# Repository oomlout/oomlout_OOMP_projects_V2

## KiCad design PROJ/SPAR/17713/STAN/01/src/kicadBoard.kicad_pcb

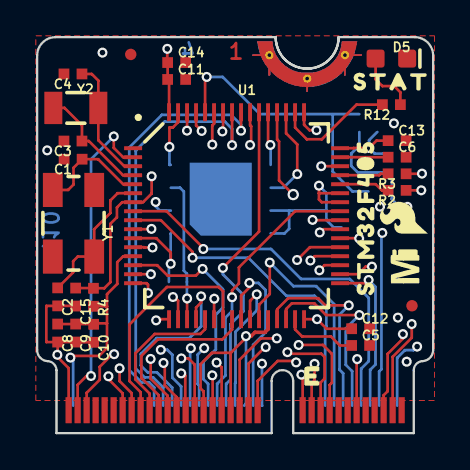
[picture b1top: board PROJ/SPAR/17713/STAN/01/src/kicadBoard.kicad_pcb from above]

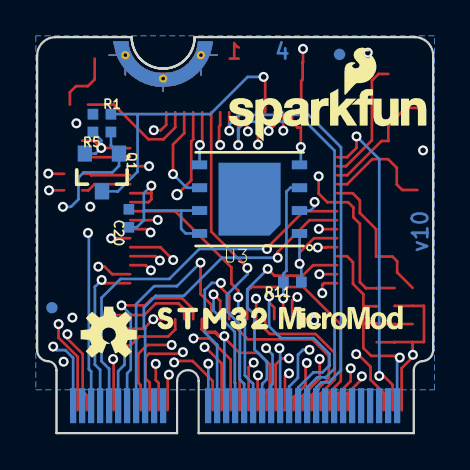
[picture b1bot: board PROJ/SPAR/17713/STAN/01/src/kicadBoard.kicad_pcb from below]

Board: 4 copper layers, 22.0 x 22.0 mm, 43 parts (12 on the bottom side), 58 nets.

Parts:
C1, C2: 22pF; 0402-TIGHT
C3, C4: 15pF; 0402-TIGHT
C5, C6: 2.2uF; 0402-TIGHT
C8, C11, C12, C13, C14, C15, C20: 0.1uF; 0402-TIGHT
C9: 1.0uF; 0402-TIGHT
C10: 4.7uF; 0402-TIGHT
D5: BLUE; LED-0603
FD1, FD2, FD3, FD4: FIDUCIALUFIDUCIAL; FIDUCIAL-MICRO
FRAME1: FRAME-LETTER; CREATIVE_COMMONS
J1: MICROMOD-2222; M.2-CARD-E-22
LOGO2: OSHW-LOGOS; OSHW-LOGO-S
LOGO3: SFE_LOGO_NAME_FLAME.1_INCH; SFE_LOGO_NAME_FLAME_.1
Q1: SOT23-3
R1, R5, R11: 100k; 0402-TIGHT
R2, R3: 22; 0402-TIGHT
R4: 5.1k; 0402-TIGHT
R12: 1k; 0402-TIGHT
U1: STM32F405RGT6; TQFP64
U3: W25QXX128MBIT-6X5; WSON-8-6X5
U$1: STAT0
U$2: STM320
U$3: MICROMOD_MI_LOGO_.35
U$4: STM32F4050
U$5: MICROMOD_LOGO_.3
U$6: SFE_LOGO_FLAME_.1
U$7: PRODUCTION_INSTRUCTIONS
Y1: 12MHz; CRYSTAL-SMD-5X3.2-4PAD
Y2: 32.768kHz; CRYSTAL-SMD-3.2X1.5MM

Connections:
3.3V: C8.1, C9.1, C10.1, C11.1, C12.1, C13.1, C14.1, C20.1, J1.2, J1.74, Q1.2, R4.2, R5.2, R11.2, U1.13, U1.19, U1.32, U1.42, U1.43, U1.48, U1.64, U3.3, U3.7, U3.8
A0: J1.34, U1.25
A1: J1.38, U1.26
AUD_BCLK: J1.50, U1.55
AUD_IN: J1.54, U1.57
AUD_LRCLK: J1.52, U1.20
AUD_OUT: J1.56, U1.56
BATT_VIN: J1.49, U1.15
BOOT0: Q1.3, R1.2, U1.60
CAN_RX: J1.41, U1.61
CAN_TX: J1.43, U1.62
CIPO: J1.61, U1.22
COPI: J1.59, U1.23
D0: J1.10, U1.8
D1: J1.18, U1.9
D+: J1.3, R3.1
D-: J1.5, R2.1
FLASH_SCK: U1.51, U3.6
FLASH_SDI: U1.53, U3.5
FLASH_SDO: U1.52, U3.2
FLASH_~CS: R11.1, U1.11, U3.1
G0: J1.40, U1.54
G1: J1.42, U1.41
G2: J1.44, U1.14
G3: J1.46, U1.39
G4: J1.48, U1.40
G5: J1.73, U1.2
G6: J1.71, U1.10
GND: C1.2, C2.2, C3.2, C4.2, C5.2, C6.2, C8.2, C9.2, C10.2, C11.2, C12.2, C13.2, C14.2, C15.2, C20.2, D5.C, J1.1, J1.7, J1.33, J1.36, J1.39, J1.45, J1.75, J1.GND1, J1.GND2, J1.GND3, R1.1, U1.12, U1.18, U1.28, U1.63, U3.4
HOST_D+: J1.35, U1.36
HOST_D-: J1.37, U1.35
HOST_ID: J1.8, U1.33
HOST_VBUS: J1.63, U1.34
unnamed: D5.A, R12.1
unnamed: R2.2, U1.44
unnamed: R3.2, U1.45
unnamed: C4.1, U1.3, Y2.P$2
unnamed: C3.1, U1.4, Y2.P$1
unnamed: C2.1, U1.6, Y1.3
unnamed: C1.1, U1.5, Y1.1
unnamed: C6.1, U1.47
unnamed: C5.1, U1.31
PWM0: J1.32, U1.37
PWM1: J1.47, U1.38
RX1: J1.19, U1.17
SCK: J1.57, U1.21
SCL: J1.14, U1.29
SCL1: J1.53, U1.58
SDA: J1.12, U1.30
SDA1: J1.51, U1.59
STAT: R12.2, U1.50
SWCLK: J1.21, U1.49
SWDIO: J1.23, U1.46
TX1: J1.17, U1.16
~BOOT: J1.11, Q1.1, R5.1
~CS: J1.55, U1.24
~INT: J1.16, U1.27
~RESET: C15.1, J1.6, R4.1, U1.7

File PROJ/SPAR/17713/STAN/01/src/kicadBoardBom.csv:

"Id";"Designator";"Package";"Quantity";"Designation";"Supplier and ref";
1;"R12";"0402-TIGHT";1;"1k";;;
2;"Y1";"CRYSTAL-SMD-5X3.2-4PAD";1;"12MHz";;;
3;"U$6";"SFE_LOGO_FLAME_.1";1;"";;;
4;"FRAME1";"CREATIVE_COMMONS";1;"FRAME-LETTER";;;
5;"R2,R3";"0402-TIGHT";2;"22";;;
6;"D5";"LED-0603";1;"BLUE";;;
7;"FD1,FD4,FD2,FD3";"FIDUCIAL-MICRO";4;"FIDUCIALUFIDUCIAL";;;
8;"C6,C5";"0402-TIGHT";2;"2.2uF";;;
9;"U$1";"STAT0";1;"";;;
10;"Y2";"CRYSTAL-SMD-3.2X1.5MM";1;"32.768kHz";;;
11;"C10";"0402-TIGHT";1;"4.7uF";;;
12;"C12,C14,C11,C8,C13,C15,C20";"0402-TIGHT";7;"0.1uF";;;
13;"J1";"M.2-CARD-E-22";1;"MICROMOD-2222";;;
14;"C2,C1";"0402-TIGHT";2;"22pF";;;
15;"C3,C4";"0402-TIGHT";2;"15pF";;;
16;"U1";"TQFP64";1;"STM32F405RGT6";;;
17;"U$7";"PRODUCTION_INSTRUCTIONS";1;"";;;
18;"U$3";"MICROMOD_MI_LOGO_.35";1;"";;;
19;"R4";"0402-TIGHT";1;"5.1k";;;
20;"C9";"0402-TIGHT";1;"1.0uF";;;
21;"U$4";"STM32F4050";1;"";;;
22;"LOGO3";"SFE_LOGO_NAME_FLAME_.1";1;"SFE_LOGO_NAME_FLAME.1_INCH";;;
23;"R11,R1,R5";"0402-TIGHT";3;"100k";;;
24;"LOGO2";"OSHW-LOGO-S";1;"OSHW-LOGOS";;;
25;"U$5";"MICROMOD_LOGO_.3";1;"";;;
26;"Q1";"SOT23-3";1;"";;;
27;"U$2";"STM320";1;"";;;
28;"U3";"WSON-8-6X5";1;"W25QXX128MBIT-6X5";;;

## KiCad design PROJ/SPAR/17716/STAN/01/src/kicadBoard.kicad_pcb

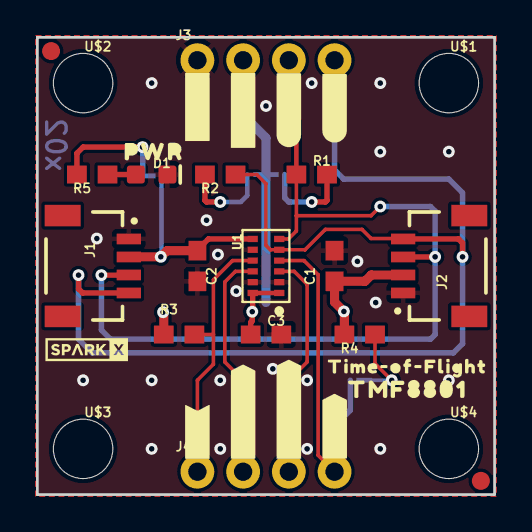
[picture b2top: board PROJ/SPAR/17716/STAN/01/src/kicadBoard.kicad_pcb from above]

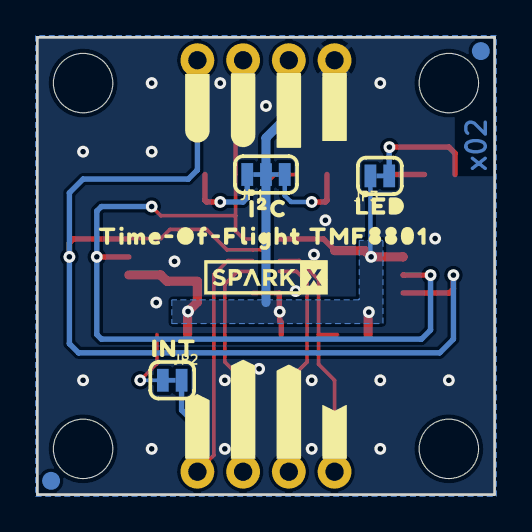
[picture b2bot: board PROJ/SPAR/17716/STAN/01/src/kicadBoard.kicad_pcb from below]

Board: 2 copper layers, 25.4 x 25.4 mm, 51 parts (18 on the bottom side), 13 nets.

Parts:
C1, C2, C3: 0.1uF; 0603
D1: RED; LED-0603
FD1, FD2, FD3, FD4: FIDUCIAL1X2; FIDUCIAL-1X2
FRAME1: FRAME-LETTERNO_PACKAGE; DUMMY
J1, J2: Qwiic; JST04_1MM_RA
J3, J4: 1X04_NO_SILK
JP1: JUMPER-SMT_3_2-NC_TRACE_SILK; SMT-JUMPER_3_2-NC_TRACE_SILK
JP2, JP3: JUMPER-SMT_2_NC_TRACE_SILK; SMT-JUMPER_2_NC_TRACE_SILK
R1, R2: 2.2k; 0603
R3, R4: 10k; 0603
R5: 1k; 0603
U1: TMF8801; TMF8801-CUSTOM
U$1, U$2, U$3, U$4: STAND-OFF
U$5, U$17: #3#3V#1
U$6, U$19: #SDA#4
U$7, U$18: #GND#0
U$8, U$24: ##INT##7
U$9, U$25: #GPIO0#7
U$10, U$26: #GPIO1#7
U$11, U$23: #EN#6
U$12: #INT0
U$13: TMF88010
U$14: TIME#OF#FLIGHT0
U$16: TIME#OF#FLIGHT_TMF88018
U$20: SPARKX-TINY
U$21, U$22: #SCL#5
U$27: SPARKX-SMALL
U$28: I�C0
U$29: LED1
U$30: PWR2

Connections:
3.3V: C1.1, C2.1, C3.1, J1.2, J2.2, J3.2, JP1.2, JP3.2, R3.2, R4.2, U1.1, U1.7, U1.12
EN: J4.1, R3.1, U1.9
GND: C1.2, C2.2, C3.2, D1.C, J1.1, J2.1, J3.1, U1.2, U1.8, U1.11
GPIO0: J4.3, U1.3
GPIO1: J4.2, U1.10
unnamed: D1.A, R5.1
unnamed: JP1.3, R1.2
unnamed: JP1.1, R2.2
unnamed: JP3.1, R5.2
unnamed: JP2.1, R4.1
SCL: J1.4, J2.4, J3.4, R2.1, U1.5
SDA: J1.3, J2.3, J3.3, R1.1, U1.6
~INT: J4.4, JP2.2, U1.4

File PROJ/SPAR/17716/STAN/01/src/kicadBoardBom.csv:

"Id";"Designator";"Package";"Quantity";"Designation";"Supplier and ref";
1;"FRAME1";"DUMMY";1;"FRAME-LETTERNO_PACKAGE";;;
2;"U$3,U$4,U$2,U$1";"STAND-OFF";4;"";;;
3;"U$5,U$17";"#3#3V#1";2;"";;;
4;"FD1,FD3,FD2,FD4";"FIDUCIAL-1X2";4;"FIDUCIAL1X2";;;
5;"U$14";"TIME#OF#FLIGHT0";1;"";;;
6;"U1";"TMF8801-CUSTOM";1;"TMF8801";;;
7;"D1";"LED-0603";1;"RED";;;
8;"U$8,U$24";"##INT##7";2;"";;;
9;"J4,J3";"1X04_NO_SILK";2;"";;;
10;"U$13";"TMF88010";1;"";;;
11;"U$20";"SPARKX-TINY";1;"";;;
12;"R3,R4";"0603";2;"10k";;;
13;"C3,C2,C1";"0603";3;"0.1uF";;;
14;"U$9,U$25";"#GPIO0#7";2;"";;;
15;"R1,R2";"0603";2;"2.2k";;;
16;"J1,J2";"JST04_1MM_RA";2;"Qwiic";;;
17;"R5";"0603";1;"1k";;;
18;"U$7,U$18";"#GND#0";2;"";;;
19;"U$11,U$23";"#EN#6";2;"";;;
20;"U$6,U$19";"#SDA#4";2;"";;;
21;"U$21,U$22";"#SCL#5";2;"";;;
22;"U$10,U$26";"#GPIO1#7";2;"";;;
23;"U$30";"PWR2";1;"";;;
24;"JP3,JP2";"SMT-JUMPER_2_NC_TRACE_SILK";2;"JUMPER-SMT_2_NC_TRACE_SILK";;;
25;"U$29";"LED1";1;"";;;
26;"U$27";"SPARKX-SMALL";1;"";;;
27;"U$16";"TIME#OF#FLIGHT_TMF88018";1;"";;;
28;"JP1";"SMT-JUMPER_3_2-NC_TRACE_SILK";1;"JUMPER-SMT_3_2-NC_TRACE_SILK";;;
29;"U$28";"I�C0";1;"";;;
30;"U$12";"#INT0";1;"";;;

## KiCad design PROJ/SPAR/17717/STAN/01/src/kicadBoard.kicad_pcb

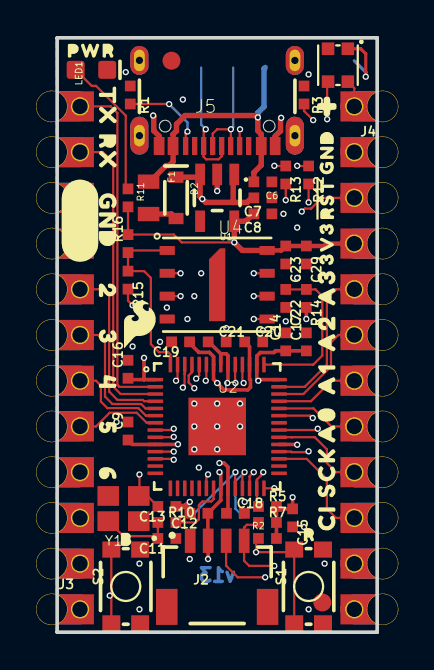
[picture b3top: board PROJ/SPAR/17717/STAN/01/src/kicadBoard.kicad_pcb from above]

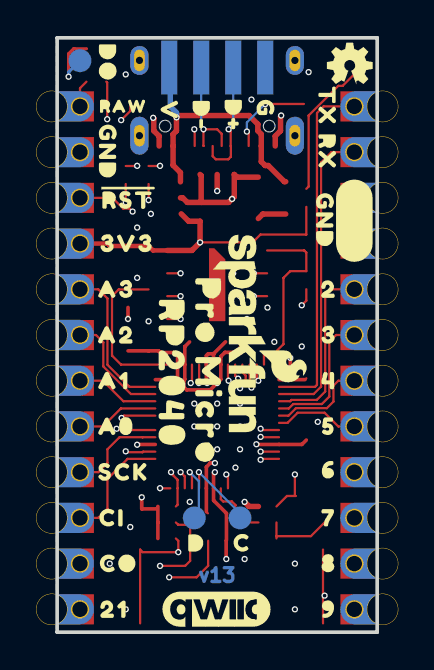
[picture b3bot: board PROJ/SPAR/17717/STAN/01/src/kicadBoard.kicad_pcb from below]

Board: 4 copper layers, 17.8 x 33.0 mm, 109 parts (39 on the bottom side), 49 nets.

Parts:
C6: 1.0uF; 0402-TIGHT
C7, C8: 10uF; 0402-TIGHT
C9, C12, C14, C15, C16, C17, C18, C19, C29: 0.1uF; 0402-TIGHT
C11, C13: 15pF; 0402-TIGHT
C20, C21, C22, C23: 2.2uF; 0402-TIGHT
D2: 3A/10V/280mV; SOD-323
F1: 6V 0.5A; 0805
FRAME2: FRAME-LEDGER; CREATIVE_COMMONS
J2: Qwiic; JST04_1MM_RA
J3, J4: 1X12_CASTELLATED
J5: USB Female Type C Connector; USB-C-16P_4LAYER-PADS
JP1, JP2: FIDUCIAL1X2; FIDUCIAL-1X2
JP14: USB_SOLDER_PADS; USB-SOLDER-PADS
LED1: RED; LED-0603
LOGO1: SFE_LOGO_NAME_FLAME.1_INCH; SFE_LOGO_NAME_FLAME_.1
LOGO3: QWIIC_LOGO_6MM; QWIIC_6MM
LOGO4: SFE_LOGO_FLAME.1_INCH; SFE_LOGO_FLAME_.1
LOGO5: SPECIAL_INSTRUCTIONS-ORDERING; ORDERING_INSTRUCTIONS
R1, R3: 5.1k; 0402-TIGHT
R2, R16: 10k; 0402-TIGHT
R5, R7: 2.2k; 0402-TIGHT
R10, R11, R15: 1k; 0402-TIGHT
R12, R13: 27; 0402-TIGHT
R14: 200; 0402-TIGHT
S1: Reset; TACTILE_SWITCH_SMD_4.6X2.8MM
S2: Boot; TACTILE_SWITCH_SMD_4.6X2.8MM
TP1, TP2, TP3: PAD.03X.05
U1: 3.3V; SOT23-5
U2: RP2040; QFN-56
U3: WS2812-2020
U4: W25QXX128MBIT; WSON-8-6X5-SKINNY_CENTERPAD
U$1, U$11: A00
U$2: GND_0
U$3: OSHW-LOGOMINI; OSHW-LOGO-MINI
U$4: PRO_MICRO0
U$5: #0
U$6: 70
U$7: 81
U$8: 92
U$9, U$64: CI4
U$10, U$67: SCK3
U$12, U$20: A10
U$13, U$33: A21
U$14, U$39: A32
U$15, U$22, U$74: GND2
U$16: 3V3_0
U$17: RAW0
U$18: C0
U$19, U$76: TX0
U$21, U$75: RX1
U$23, U$53: 20
U$24, U$54: 31
U$25, U$55: 42
U$26, U$56: 53
U$27, U$57: 64
U$28: D#1
U$29: D#2
U$30: G0
U$31: V3
U$32: 210
U$34: #RST#0
U$35: D1
U$36: B0
U$37: R0
U$38: RP20401
U$40: DO0
U$66: CO5
U$68: #RST#1
U$69: 3V30
U$73: PWR0
Y1: 12MHz; CRYSTAL-SMD-2X2.5MM

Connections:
0/TX0: J3.12, J3.12B, U2.2
1.1V: C18.1, C19.1, C20.1, U2.23, U2.45, U2.50
1/RX0: J3.11, J3.11B, U2.3
2: J3.8, J3.8B, U2.4
3: J3.7, J3.7B, U2.5
3.3V: C8.2, C9.1, C12.1, C14.1, C15.1, C16.1, C17.1, C21.1, C23.1, C29.1, J2.2, J4.4, J4.4B, R2.2, R5.2, R7.2, R11.2, R14.2, R16.2, U1.5, U2.1, U2.10, U2.22, U2.33, U2.42, U2.44, U2.48, U2.49, U4.8
4: J3.6, J3.6B, U2.6
5: J3.5, J3.5B, U2.7
6: J3.4, J3.4B, U2.8
7: J3.3, J3.3B, U2.9
8/TX1: J3.2, J3.2B, U2.11
9/RX1: J3.1, J3.1B, U2.12
16/SDA: J2.3, R5.1, U2.27
17/SCL: J2.4, R7.1, U2.28
20/SPI_CIPO: J4.10, J4.10B, U2.31
21/SPI_~CS: J4.12, J4.12B, U2.32
22/SPI_SCK: J4.9, J4.9B, U2.34
23/SPI_COPI: J4.11, J4.11B, U2.35
25/WS2812-DI: U2.37, U3.3
A0: J4.8, J4.8B, U2.38
A1: J4.7, J4.7B, U2.39
A2: J4.6, J4.6B, U2.40
A3: J4.5, J4.5B, U2.41
ADC_VDD: C22.1, R14.1, U2.43
BOOT: R15.2, S2.3, S2.4
GND: C6.1, C7.1, C8.1, C9.2, C11.1, C12.2, C13.1, C14.2, C15.2, C16.2, C17.2, C18.2, C19.2, C20.2, C21.2, C22.2, C23.2, C29.2, J2.1, J3.9, J3.9B, J3.10, J3.10B, J4.2, J4.2B, J5.GND, J5.GND2, JP14.GND, LED1.C, R1.1, R3.1, S1.1, S1.2, S2.1, S2.2, U1.2, U2.19, U2.EPAD, U3.2, U4.4
unnamed: TP3.P$1, U3.1
unnamed: J5.A5, R3.2
unnamed: J5.B5, R1.2
unnamed: LED1.A, R11.1
QSPI-0: U2.53, U4.5
QSPI-1: U2.55, U4.2
QSPI-2: U2.54, U4.3
QSPI-3: U2.51, U4.7
QSPI-CLK: U2.52, U4.6
QSPI-CS: R15.1, R16.1, U2.56, U4.1
RAW: C7.2, D2.C, J4.1, J4.1B, U1.1, U1.3, U3.4
RP_D1+: R13.2, U2.47
RP_D1-: R12.2, U2.46
RP_D+: J5.A6, J5.B6, JP14.D+, R13.1
RP_D-: J5.A7, J5.B7, JP14.D-, R12.1
SWDCK: TP1.P$1, U2.24
SWDIO: TP2.P$1, U2.25
USB_RAW: D2.A, F1.2
V_USB: C6.2, F1.1, J5.VBUS1, J5.VBUS2, JP14.VBUS
X1A: R10.2, U2.21
X1B: C11.2, R10.1, Y1.P1
X2: C13.2, U2.20, Y1.P3
~RESET: J4.3, J4.3B, R2.1, S1.3, S1.4, U2.26

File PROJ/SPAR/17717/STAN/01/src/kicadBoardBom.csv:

"Id";"Designator";"Package";"Quantity";"Designation";"Supplier and ref";
1;"R16,R2";"0402-TIGHT";2;"10k";;;
2;"U$68";"#RST#1";1;"";;;
3;"J2";"JST04_1MM_RA";1;"Qwiic";;;
4;"U$1,U$11";"A00";2;"";;;
5;"U2";"QFN-56";1;"RP2040";;;
6;"U1";"SOT23-5";1;"3.3V";;;
7;"C18,C15,C9,C16,C29,C19,C17,C14,C12";"0402-TIGHT";9;"0.1uF";;;
8;"U$69";"3V30";1;"";;;
9;"R1,R3";"0402-TIGHT";2;"5.1k";;;
10;"LOGO5";"ORDERING_INSTRUCTIONS";1;"SPECIAL_INSTRUCTIONS-ORDERING";;;
11;"F1";"0805";1;"6V 0.5A";;;
12;"JP1,JP2";"FIDUCIAL-1X2";2;"FIDUCIAL1X2";;;
13;"U3";"WS2812-2020";1;"WS2812-2020";;;
14;"U$5";"#0";1;"";;;
15;"U$64,U$9";"CI4";2;"";;;
16;"U$53,U$23";"20";2;"";;;
17;"FRAME2";"CREATIVE_COMMONS";1;"FRAME-LEDGER";;;
18;"D2";"SOD-323";1;"3A/10V/280mV";;;
19;"U$39,U$14";"A32";2;"";;;
20;"R10,R11,R15";"0402-TIGHT";3;"1k";;;
21;"S1";"TACTILE_SWITCH_SMD_4.6X2.8MM";1;"Reset";;;
22;"U$36";"B0";1;"";;;
23;"U$57,U$27";"64";2;"";;;
24;"R5,R7";"0402-TIGHT";2;"2.2k";;;
25;"U$67,U$10";"SCK3";2;"";;;
26;"C13,C11";"0402-TIGHT";2;"15pF";;;
27;"LED1";"LED-0603";1;"RED";;;
28;"J3,J4";"1X12_CASTELLATED";2;"";;;
29;"C6";"0402-TIGHT";1;"1.0uF";;;
30;"U$73";"PWR0";1;"";;;
31;"R14";"0402-TIGHT";1;"200";;;
32;"J5";"USB-C-16P_4LAYER-PADS";1;"USB Female Type C Connector";;;
33;"C21,C20,C23,C22";"0402-TIGHT";4;"2.2uF";;;
34;"U$74,U$22,U$15";"GND2";3;"";;;
35;"U4";"WSON-8-6X5-SKINNY_CENTERPAD";1;"W25QXX128MBIT";;;
36;"U$33,U$13";"A21";2;"";;;
37;"U$37";"R0";1;"";;;
38;"C8,C7";"0402-TIGHT";2;"10uF";;;
39;"U$55,U$25";"42";2;"";;;
40;"R12,R13";"0402-TIGHT";2;"27";;;
41;"S2";"TACTILE_SWITCH_SMD_4.6X2.8MM";1;"Boot";;;
42;"U$75,U$21";"RX1";2;"";;;
43;"U$76,U$19";"TX0";2;"";;;
44;"U$2";"GND_0";1;"";;;
45;"U$20,U$12";"A10";2;"";;;
46;"U$56,U$26";"53";2;"";;;
47;"U$54,U$24";"31";2;"";;;
48;"LOGO4";"SFE_LOGO_FLAME_.1";1;"SFE_LOGO_FLAME.1_INCH";;;
49;"Y1";"CRYSTAL-SMD-2X2.5MM";1;"12MHz";;;
50;"U$32";"210";1;"";;;
51;"TP2,TP3,TP1";"PAD.03X.05";3;"";;;
52;"U$7";"81";1;"";;;
53;"U$31";"V3";1;"";;;
54;"U$35";"D1";1;"";;;
55;"U$28";"D#1";1;"";;;
56;"U$8";"92";1;"";;;
57;"LOGO1";"SFE_LOGO_NAME_FLAME_.1";1;"SFE_LOGO_NAME_FLAME.1_INCH";;;
58;"U$38";"RP20401";1;"";;;
59;"U$66";"CO5";1;"";;;
60;"JP14";"USB-SOLDER-PADS";1;"USB_SOLDER_PADS";;;
61;"U$3";"OSHW-LOGO-MINI";1;"OSHW-LOGOMINI";;;
62;"U$4";"PRO_MICRO0";1;"";;;
63;"U$34";"#RST#0";1;"";;;
64;"U$18";"C0";1;"";;;
65;"U$29";"D#2";1;"";;;
66;"LOGO3";"QWIIC_6MM";1;"QWIIC_LOGO_6MM";;;
67;"U$17";"RAW0";1;"";;;
68;"U$6";"70";1;"";;;
69;"U$16";"3V3_0";1;"";;;
70;"U$40";"DO0";1;"";;;
71;"U$30";"G0";1;"";;;

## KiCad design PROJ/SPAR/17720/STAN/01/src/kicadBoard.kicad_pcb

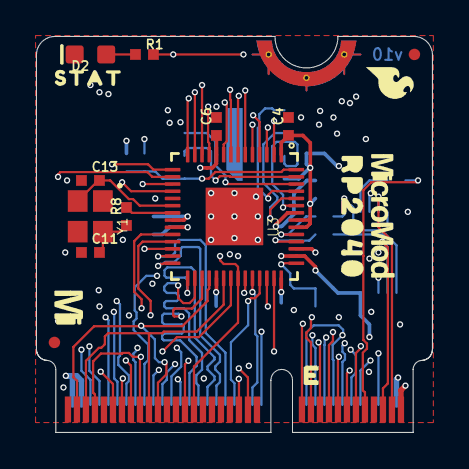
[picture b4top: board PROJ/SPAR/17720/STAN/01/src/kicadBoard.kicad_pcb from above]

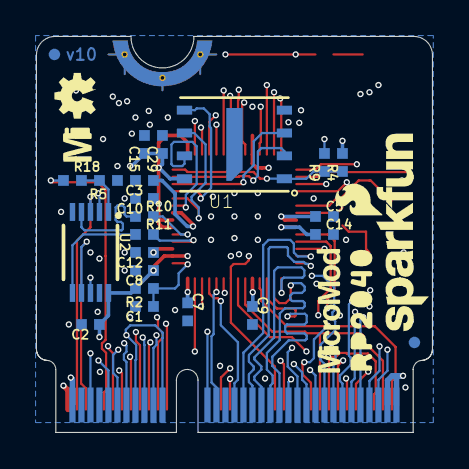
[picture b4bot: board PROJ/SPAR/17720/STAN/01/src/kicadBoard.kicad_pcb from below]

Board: 4 copper layers, 22.0 x 22.0 mm, 47 parts (28 on the bottom side), 58 nets.

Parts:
C1, C3, C4, C15: 2.2uF; 0402-TIGHT
C2, C5, C6, C7, C8, C9, C10, C12, C14, C29: 0.1uF; 0402-TIGHT
C11, C13: 15pF; 0402-TIGHT
D2: BLUE; LED-0603
FD1, FD2, FD3, FD4: FIDUCIALUFIDUCIAL; FIDUCIAL-MICRO
FRAME1: FRAME-LEDGER; CREATIVE_COMMONS
J1: MICROMOD-2222; M.2-CARD-E-22
LOGO1: SFE_LOGO_NAME_FLAME.1_INCH; SFE_LOGO_NAME_FLAME_.1
LOGO2: SFE_LOGO_FLAME.1_INCH; SFE_LOGO_FLAME_.1
LOGO3: OSHW-LOGOMINI; OSHW-LOGO-MINI
LOGO4: SPECIAL_INSTRUCTIONS-ORDERING; ORDERING_INSTRUCTIONS
R1, R8, R9, R18: 1k; 0402-TIGHT
R2: 200OHM-0402T-1/16W-1%; 0402-TIGHT
R4, R5: 10k; 0402-TIGHT
R10, R11: 27; 0402-TIGHT
U1: W25QXX128MBIT; WSON-8-6X5-SKINNY_CENTERPAD
U2: FSUSB30MUX_MSOP10; MSOP10
U3: RP2040; QFN-56
U$1, U$7: MICROMOD_MI_LOGO_.35
U$3, U$12: MICROMOD_LOGO_.3
U$4, U$9: RP20400
U$11: STAT0
Y1: 12MHz; CRYSTAL-SMD-2X2.5MM

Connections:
1.1V: C3.1, C12.1, C14.1, U3.23, U3.45, U3.50
3.3V: C2.1, C4.1, C5.1, C6.1, C7.1, C8.1, C9.1, C10.1, C15.1, C29.1, J1.2, J1.72, J1.74, R2.2, R4.2, U1.8, U2.10, U3.1, U3.10, U3.22, U3.33, U3.42, U3.44, U3.48, U3.49
A0: J1.34, U3.38
A1: J1.38, U3.39
ADC_VDD: C1.1, R2.1, U3.43
BATT_VIN/3: J1.49, U3.41
BOOT: J1.11, R9.2
CTS1/AUD_LRCLK: J1.15, J1.52, U3.4
D0: J1.10, U3.8
D1: J1.18, U3.9
G0: J1.40, U3.27
G1: J1.42, U3.28
G2: J1.44, U3.29
G3: J1.46, U3.30
G9: J1.65, U3.40
GND: C1.2, C2.2, C3.2, C4.2, C5.2, C6.2, C7.2, C8.2, C9.2, C10.2, C11.1, C12.2, C13.1, C14.2, C15.2, C29.2, D2.C, J1.1, J1.7, J1.33, J1.36, J1.39, J1.45, J1.75, J1.GND1, J1.GND2, J1.GND3, R5.1, U1.4, U2.5, U2.9, U3.19, U3.EPAD
I2C_~INT/TX2: J1.16, J1.22, U3.11
LED_BUILTIN/G10: J1.63, R1.2, U3.37
unnamed: D2.A, R1.1
unnamed: R8.2, U3.21
unnamed: C13.2, U3.20, Y1.P3
unnamed: C11.2, R8.1, Y1.P1
PWM0: J1.32, U3.16
PWM1/AUD_MCLK: J1.47, J1.58, U3.36
QSPI-0: U1.5, U3.53
QSPI-1: U1.2, U3.55
QSPI-2: U1.3, U3.54
QSPI-3: U1.7, U3.51
QSPI-CLK: U1.6, U3.52
QSPI-CS: R4.1, R9.1, U1.1, U3.56
RP_D1+: R10.2, U3.47
RP_D1-: R11.2, U3.46
RP_D+: R10.1, U2.4
RP_D-: R11.1, U2.6
RTS1/AUD_BCLK: J1.13, J1.50, U3.5
RX1: J1.19, U3.3
SCL: J1.14, U3.7
SDA: J1.12, U3.6
SDIO_DAT1/AUD_IN: J1.54, J1.66, U3.14
SDIO_DAT2/AUD_OUT: J1.56, J1.68, U3.13
SPI_CIPO1/SDIO_DAT0: J1.64, U3.15
SPI_CIPO/G4: J1.48, J1.61, U3.31
SPI_COPI1/SDIO_CMD: J1.62, U3.18
SPI_COPI/G7: J1.59, J1.69, U3.35
SPI_SCK1/SDIO_CLK: J1.60, U3.17
SPI_SCK/G6: J1.57, J1.71, U3.34
SPI_~CS1/SDIO_DAT3/RX2: J1.20, J1.70, U3.12
SPI_~CS/G5: J1.55, J1.73, U3.32
SWDCK: J1.21, U3.24
SWDIO: J1.23, U3.25
TX1: J1.17, U3.2
USBHOST_D+: J1.35, U2.2
USBHOST_D-: J1.37, U2.8
USB_D+: J1.3, U2.3
USB_D-: J1.5, U2.7
USB_MUX_SIG: R5.2, R18.2, U2.1
USB_VIN: J1.9, R18.1
~RESET: J1.6, U3.26

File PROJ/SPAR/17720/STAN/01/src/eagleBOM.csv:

"Part";"Value";"Device";"Package";"Description";"DESIGNER";"PROD_ID";"REV";"VALUE";
"C1";"2.2uF";"2.2UF-0402_TIGHT-10V-10%-X5R";"0402-TIGHT";"2.2µF ceramic capacitors";"";"CAP-14232";"";"2.2uF";
"C2";"0.1uF";"0.1UF-0402T-6.3V-10%-X7R";"0402-TIGHT";"0.1µF ceramic capacitors";"";"CAP-14993";"";"0.1uF";
"C3";"2.2uF";"2.2UF-0402_TIGHT-10V-10%-X5R";"0402-TIGHT";"2.2µF ceramic capacitors";"";"CAP-14232";"";"2.2uF";
"C4";"2.2uF";"2.2UF-0402_TIGHT-10V-10%-X5R";"0402-TIGHT";"2.2µF ceramic capacitors";"";"CAP-14232";"";"2.2uF";
"C5";"0.1uF";"0.1UF-0402T-6.3V-10%-X7R";"0402-TIGHT";"0.1µF ceramic capacitors";"";"CAP-14993";"";"0.1uF";
"C6";"0.1uF";"0.1UF-0402T-6.3V-10%-X7R";"0402-TIGHT";"0.1µF ceramic capacitors";"";"CAP-14993";"";"0.1uF";
"C7";"0.1uF";"0.1UF-0402T-6.3V-10%-X7R";"0402-TIGHT";"0.1µF ceramic capacitors";"";"CAP-14993";"";"0.1uF";
"C8";"0.1uF";"0.1UF-0402T-6.3V-10%-X7R";"0402-TIGHT";"0.1µF ceramic capacitors";"";"CAP-14993";"";"0.1uF";
"C9";"0.1uF";"0.1UF-0402T-6.3V-10%-X7R";"0402-TIGHT";"0.1µF ceramic capacitors";"";"CAP-14993";"";"0.1uF";
"C10";"0.1uF";"0.1UF-0402T-6.3V-10%-X7R";"0402-TIGHT";"0.1µF ceramic capacitors";"";"CAP-14993";"";"0.1uF";
"C11";"15pF";"15PF-0402T-50V-5%";"0402-TIGHT";"15pF ceramic capacitors";"";"CAP-13063";"";"15pF";
"C12";"0.1uF";"0.1UF-0402T-6.3V-10%-X7R";"0402-TIGHT";"0.1µF ceramic capacitors";"";"CAP-14993";"";"0.1uF";
"C13";"15pF";"15PF-0402T-50V-5%";"0402-TIGHT";"15pF ceramic capacitors";"";"CAP-13063";"";"15pF";
"C14";"0.1uF";"0.1UF-0402T-6.3V-10%-X7R";"0402-TIGHT";"0.1µF ceramic capacitors";"";"CAP-14993";"";"0.1uF";
"C15";"2.2uF";"2.2UF-0402_TIGHT-10V-10%-X5R";"0402-TIGHT";"2.2µF ceramic capacitors";"";"CAP-14232";"";"2.2uF";
"C29";"0.1uF";"0.1UF-0402T-6.3V-10%-X7R";"0402-TIGHT";"0.1µF ceramic capacitors";"";"CAP-14993";"";"0.1uF";
"D2";"BLUE";"LED-BLUE0603";"LED-0603";"Blue SMD LED";"";"DIO-08575";"";"BLUE";
"FD1";"FIDUCIALUFIDUCIAL";"FIDUCIALUFIDUCIAL";"FIDUCIAL-MICRO";"Fiducial Alignment Points";"";"";"";"";
"FD2";"FIDUCIALUFIDUCIAL";"FIDUCIALUFIDUCIAL";"FIDUCIAL-MICRO";"Fiducial Alignment Points";"";"";"";"";
"FD3";"FIDUCIALUFIDUCIAL";"FIDUCIALUFIDUCIAL";"FIDUCIAL-MICRO";"Fiducial Alignment Points";"";"";"";"";
"FD4";"FIDUCIALUFIDUCIAL";"FIDUCIALUFIDUCIAL";"FIDUCIAL-MICRO";"Fiducial Alignment Points";"";"";"";"";
"FRAME1";"FRAME-LEDGER";"FRAME-LEDGER";"CREATIVE_COMMONS";"Schematic Frame - Ledger";"";"";"";"";
"J1";"MICROMOD-2222";"MICROMOD-2222";"M.2-CARD-E-22";"MicroMod Connector";"";"";"";"";
"LOGO1";"SFE_LOGO_NAME_FLAME.1_INCH";"SFE_LOGO_NAME_FLAME.1_INCH";"SFE_LOGO_NAME_FLAME_.1";"SparkFun Font Logo w/ Flame";"";"";"";"";
"LOGO2";"SFE_LOGO_FLAME.1_INCH";"SFE_LOGO_FLAME.1_INCH";"SFE_LOGO_FLAME_.1";"SparkFun Flame Logo";"";"";"";"";
"LOGO3";"OSHW-LOGOMINI";"OSHW-LOGOMINI";"OSHW-LOGO-MINI";"Open-Source Hardware (OSHW) Logo";"";"";"";"";
"LOGO4";"SPECIAL_INSTRUCTIONS-ORDERING";"SPECIAL_INSTRUCTIONS-ORDERING";"ORDERING_INSTRUCTIONS";"Special Ordering/Production Instructions Alert";"";"";"";"";
"R1";"1k";"1KOHM-0402T-1/16W-1%";"0402-TIGHT";"1kΩ resistor";"";"RES-14342";"";"1k";
"R2";"200OHM-0402T-1/16W-1%";"200OHM-0402T-1/16W-1%";"0402-TIGHT";"200Ω resistor";"";"RES-15550";"";"";
"R4";"10k";"10KOHM-0402T-1/16W-1%";"0402-TIGHT";"10kΩ resistor";"";"RES-14241";"";"10k";
"R5";"10k";"10KOHM-0402T-1/16W-1%";"0402-TIGHT";"10kΩ resistor";"";"RES-14241";"";"10k";
"R8";"1k";"1KOHM-0402T-1/16W-1%";"0402-TIGHT";"1kΩ resistor";"";"RES-14342";"";"1k";
"R9";"1k";"1KOHM-0402T-1/16W-1%";"0402-TIGHT";"1kΩ resistor";"";"RES-14342";"";"1k";
"R10";"27";"27OHM";"0402-TIGHT";"27Ω resistor";"";"RES-15238";"";"";
"R11";"27";"27OHM";"0402-TIGHT";"27Ω resistor";"";"RES-15238";"";"";
"R18";"1k";"1KOHM-0402T-1/16W-1%";"0402-TIGHT";"1kΩ resistor";"";"RES-14342";"";"1k";
"U1";"W25QXX128MBIT";"W25QXX128MBIT-6X5-SKINNY_CENTER";"WSON-8-6X5-SKINNY_CENTERPAD";"";"";"IC-15107";"";"";
"U2";"FSUSB30MUX_MSOP10";"FSUSB30MUX_MSOP10";"MSOP10";"";"";"IC-15569";"";"";
"U3";"RP2040";"RP2040";"QFN-56";"Raspberry Pi RP2040 MCU";"";"IC-15502";"";"";
"Y1";"12MHz";"CRYSTAL-12MHZ";"CRYSTAL-SMD-2X2.5MM";"12.0MHz Crystal";"";"XTAL-15540";"";"";

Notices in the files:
parts and their libraries:
RELEASED UNDER THE CREATIVE COMMONS ATTRIBUTION SHARE-ALIKE 4.0 LICENSE
HTTPS://CREATIVECOMMONS.ORG/LICENSES/BY-SA/4.0
